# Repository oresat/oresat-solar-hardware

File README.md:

# OreSat Solar Modules

This repo contains the CAD for [OreSat's](oresat.org) solar modules. Part of OreSat's design is a module bus system that spans 1 - 3 U, so each array is its own 1U "panel". Oresat0, a 1U CubeSat, thus has 4 solar modules, and OreSat1, a 2U CubeSat, has 8. This approach has pretty severe drawbacks in terms of solar cell coverage area, but it's extremely flexible for having one design across a bunch of different designs. One nifty part of this design is that each 1u panel has its own **true** maximum power point tracker, with a software-defined MPPT algorithm. We're MPPT elitists - we eschew maximum power point "controllers" and think if it's not doing true power point optimization, you're just doing it wrong.

That and coffee. You're all doing coffee wrong, too, but we don't hold that against you, you don't live in Portland, we understand.

We've flown our GaAs solar cell design, and are currently workingon our silicon design.

# Design Notes

**Status, design, construction, and testing information can be found in the [OreSat Solar Module Design Notes](https://docs.google.com/document/d/1mogZjYhJievwLsnVkg4Q0sEF9xPMA5q7KPciky3YWKE/edit?usp=sharing).**

# Pretty Pictures

## LICENSE

Copyright the Portland State Aerospace Society, 2025.

This source describes Open Hardware that is licensed under CERN-OHL-S v2, or any later version.

You may redistribute and modify this source and make products using it under the terms of the CERN-OHL-S v2 (https://ohwr.org/cern_ohl_s_v2.txt).

This source is distributed WITHOUT ANY EXPRESS OR IMPLIED WARRANTY, INCLUDING OF MERCHANTABILITY, SATISFACTORY QUALITY AND FITNESS FOR A PARTICULAR PURPOSE. Please see the CERN-OHL-S v2 for applicable conditions.

Source location: https://github.com/oresat/

If you require a different license for this open hardware project, please contact us at [oresat@pdx.edu](mailto:oresat@pdx.edu).

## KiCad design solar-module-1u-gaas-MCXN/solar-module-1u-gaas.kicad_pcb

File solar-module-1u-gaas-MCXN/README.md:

---
title: "**OreSat Solar Module with GaAs Cells and MCXN processor**"
subtitle: |
  **Fabrication and Assembly Information**\
  For build TIME-STAMP
fontsize: 10pt
geometry:
  - margin=0.5in
toc: true
toc-depth: 2
colorlinks: true
urlcolor: blue
---

\newpage

# About this Board

## Board Description

This PCB is for the OreSat "1U" solar module which is used for all OreSat 1 - 3U designs. It has GaAs and Si solar cell variants, as well as STM32 and MCXN microcontorller variants. This design is the GaAs + MCXN version. It is scheduled to fly on OreSat1. 

The solar module takes power from the solar cells and does true maximum power point tracking (MPPT) using the Perturb and Observe ("P&O") method. It boosts the cell voltage up to 8.2 V in order to directly charge the batteries.

## Documentation Links

- Git repository: <https://github.com/oresat/oresat-solar-hardware>
- [Design Notes](https://docs.google.com/document/d/1mogZjYhJievwLsnVkg4Q0sEF9xPMA5q7KPciky3YWKE/edit?usp=sharing)

## Documentation Files

| Filename                        | Notes                                    |
| ------------------------------- | ---------------------------------------- |
| README.pdf                      | This README file                         |
| PROJECT-NAME-outline.dxf        | Board outline (with holes) in DXF format |
| PROJECT-NAME-pcba.step          | 3D model of PCBA (with components)       |
| PROJECT-NAME-render-bot.jpg     | Render of the top of the 3D model        |
| PROJECT-NAME-render-bot.jpg     | Render of the bottom of the 3D model     |
| PROJECT-NAME-schematic.pdf      | PDF of board schematics                  |

## Contact Information

- Website: <https://www.oresat.org/>
- Email: <oresat@pdx.edu>
- Instagram: @pdxaerospace

## Board Renders

{width=50%}
{width=50%}

\newpage

# Printed Circuit Board (PCB) Fabrication Information

## Board Info

- 4 layer board
- Bounding box is 83.0 x 100.0 mm
- Board thickness is 1.59 mm

## Board Requirements

- Design Rules
    - Minimum Trace / Space design rules
       - Outer layers: 0.127 mm (5.0 mil) / 0.127 mm (5.0 mil)
       - Inner layers: 0.127 mm (5.0 mil) / 0.127 mm (5.0 mil)
    - Outer dimension router tolerance: +/- 0.254 mm (10.0 mil)
    - Hole placement tolerance: +/- 0.075 mm (3.0 mil)
    - Inner tab routed slot tolerance: +/- 0.254 mm (10.0 mil)
- Drills
   - Drill Positional Tolerance: 0.051 mm (2.0 mil)
   - Drill Size tolerance: +/- 0.064 mm (2.5 mil)
- Plated/Un-plated holes
  - Via/PTH minimum diameter: 0.254 mm (10 mil)
  - Via/PTH minimum annulus: 0.102 mm (4 mil) radius
- Outline/Routing
  - This board requires a 1 mm router bit.
- Slots/Cutouts
  - There are six cutouts in the board.
- There are 3 fiducials on the top layer.
- Panel tabs ("mouse bites")
   - Card edges must be smooth; no mouse bites or other intrusions into the card outline.
   - If external mouse bites are required, minimize and customer will remove by hand before assembly.
- If not otherwise specified, build to IPC 6012 Class 2 or better.

## Stackup /  Materials

- Outside copper layers is 1 oz Cu after plating (0.043 mm / 1.7 mil)
- Inside copper layers are 0.5 oz Cu (0.018 mm / 0.7 mil)
- There are no requirements on the prepreg or core of this four layer stackup.
- Board Surface treatment should be ENIG, althogh immersion Silver is acceptable.
- White silkscreen on top and bottom surface
- Taiyo PSR-4000 or equivalent soldermask on top and bottom, no requirements for color.

## Array / Panel Information

- Coordinate with Contract Manufacturer (CM) for optimal size of this panel.
- If no feedback from CM, then produce single boards (no panel).

## Fabrication Files

### IPC-2581 File

| Filename                 | Notes                                   |
| ------------------------ | --------------------------------------- |
| PROJECT-NAME-ipc2581.xml | IPC-2581 board information file         |

### Legacy PCB Files

| Filename                      | Notes                                         |
| ------------------------------| --------------------------------------------- |
| PROJECT-NAME-Edge_Cuts.gbr    | RS274X file for the dimension (outline) layer |
| PROJECT-NAME-F_Silkscreen.gbr | RS274X file for the top silkscreen            |
| PROJECT-NAME-F_Mask.gbr       | RS274X file for the top soldermask            |
| PROJECT-NAME-F_Cu.gbr         | RS274X file for the top copper layer          |
| PROJECT-NAME-In1_Cu.gbr       | RS274X file for the layer 2 copper            |
| PROJECT-NAME-In2_Cu.gbr       | RS274X file for the layer 3 copper            |
| PROJECT-NAME-B_Cu.gbr         | RS274X file for the bottom copper layer       |
| PROJECT-NAME-B_Mask.gbr       | RS274X file for the bottom soldermask         |
| PROJECT-NAME-B_Silkscreen.gbr | RS274X file for the bottom silkscreen         |
| PROJECT-NAME-NPTH.drl         | Excellon file for non-plated through holes    |
| PROJECT-NAME-PTH.drl          | Excellon file for plated through holes        | 

\newpage

# Printed Circuit Board Assembly (PCBA) Information

## Assembly Info

- All components are on the top side of the board.
- This PCBA uses only surface mount (SMT) components.

## Assembly Requirements

- Assemble to IPC Class 2 or better
- Bake components that are not moisture sealed to appropriate levels as required.
- Solder paste MUST be leaded.
- Aqueous flux and wash strongly preferred.
   - Clean to NASA Standard "Visibly Clean (VC)": No particles or residues are visible to the naked eye.
- No conformal coating.
- Ship in antistatic protective bag

## Component Specific Assembly Information

- U2 and U7 are hand installed upside down; see ["PSAS SOP - TMP101 Mounting on Solar MOdules"](https://docs.google.com/document/d/1C_-naV0ThPKOAYU6vSqqT_bxouM6lSOQ0vK8YNHYac8/edit?usp=sharing).
- Solar Cells D2 and D6 are hand placed; see ["PSAS SOP - Solar Cell mounting with PSA"](https://docs.google.com/document/d/1PRLbhDLpztdpU8TQuk0uR0zjref0UoxRCXlIfN_OXDI/edit?usp=sharing).

## Assembly Files

### IPC-2581 File

| Filename                 | Notes                           |
| ------------------------ | ------------------------------- |
| PROJECT-NAME-ipc2581.xml | IPC-2581 board information file |

### Bill of Materials (BOM)

| Filename             | Description                            |
| -------------------- | -------------------------------------- |
| PROJECT-NAME-bom.csv | BOM in Comma Separated Variable format |

### Solder Paste Stencils

| Filename                 | Notes                                            |
| ------------------------ | ------------------------------------------------ |
| PROJECT-NAME-B_Paste.gbr | RS274X file for top/front solder paste stencil   |
| PROJECT-NAME-F_Paste.gbr | RS274X file for bottom/back solder paste stencil |

### Mounting/Placement Location

| Filename            | Description                                 |
| ------------------- | ------------------------------------------- |
| PROJECT-NAME.pos | Pick and place locations for components     |

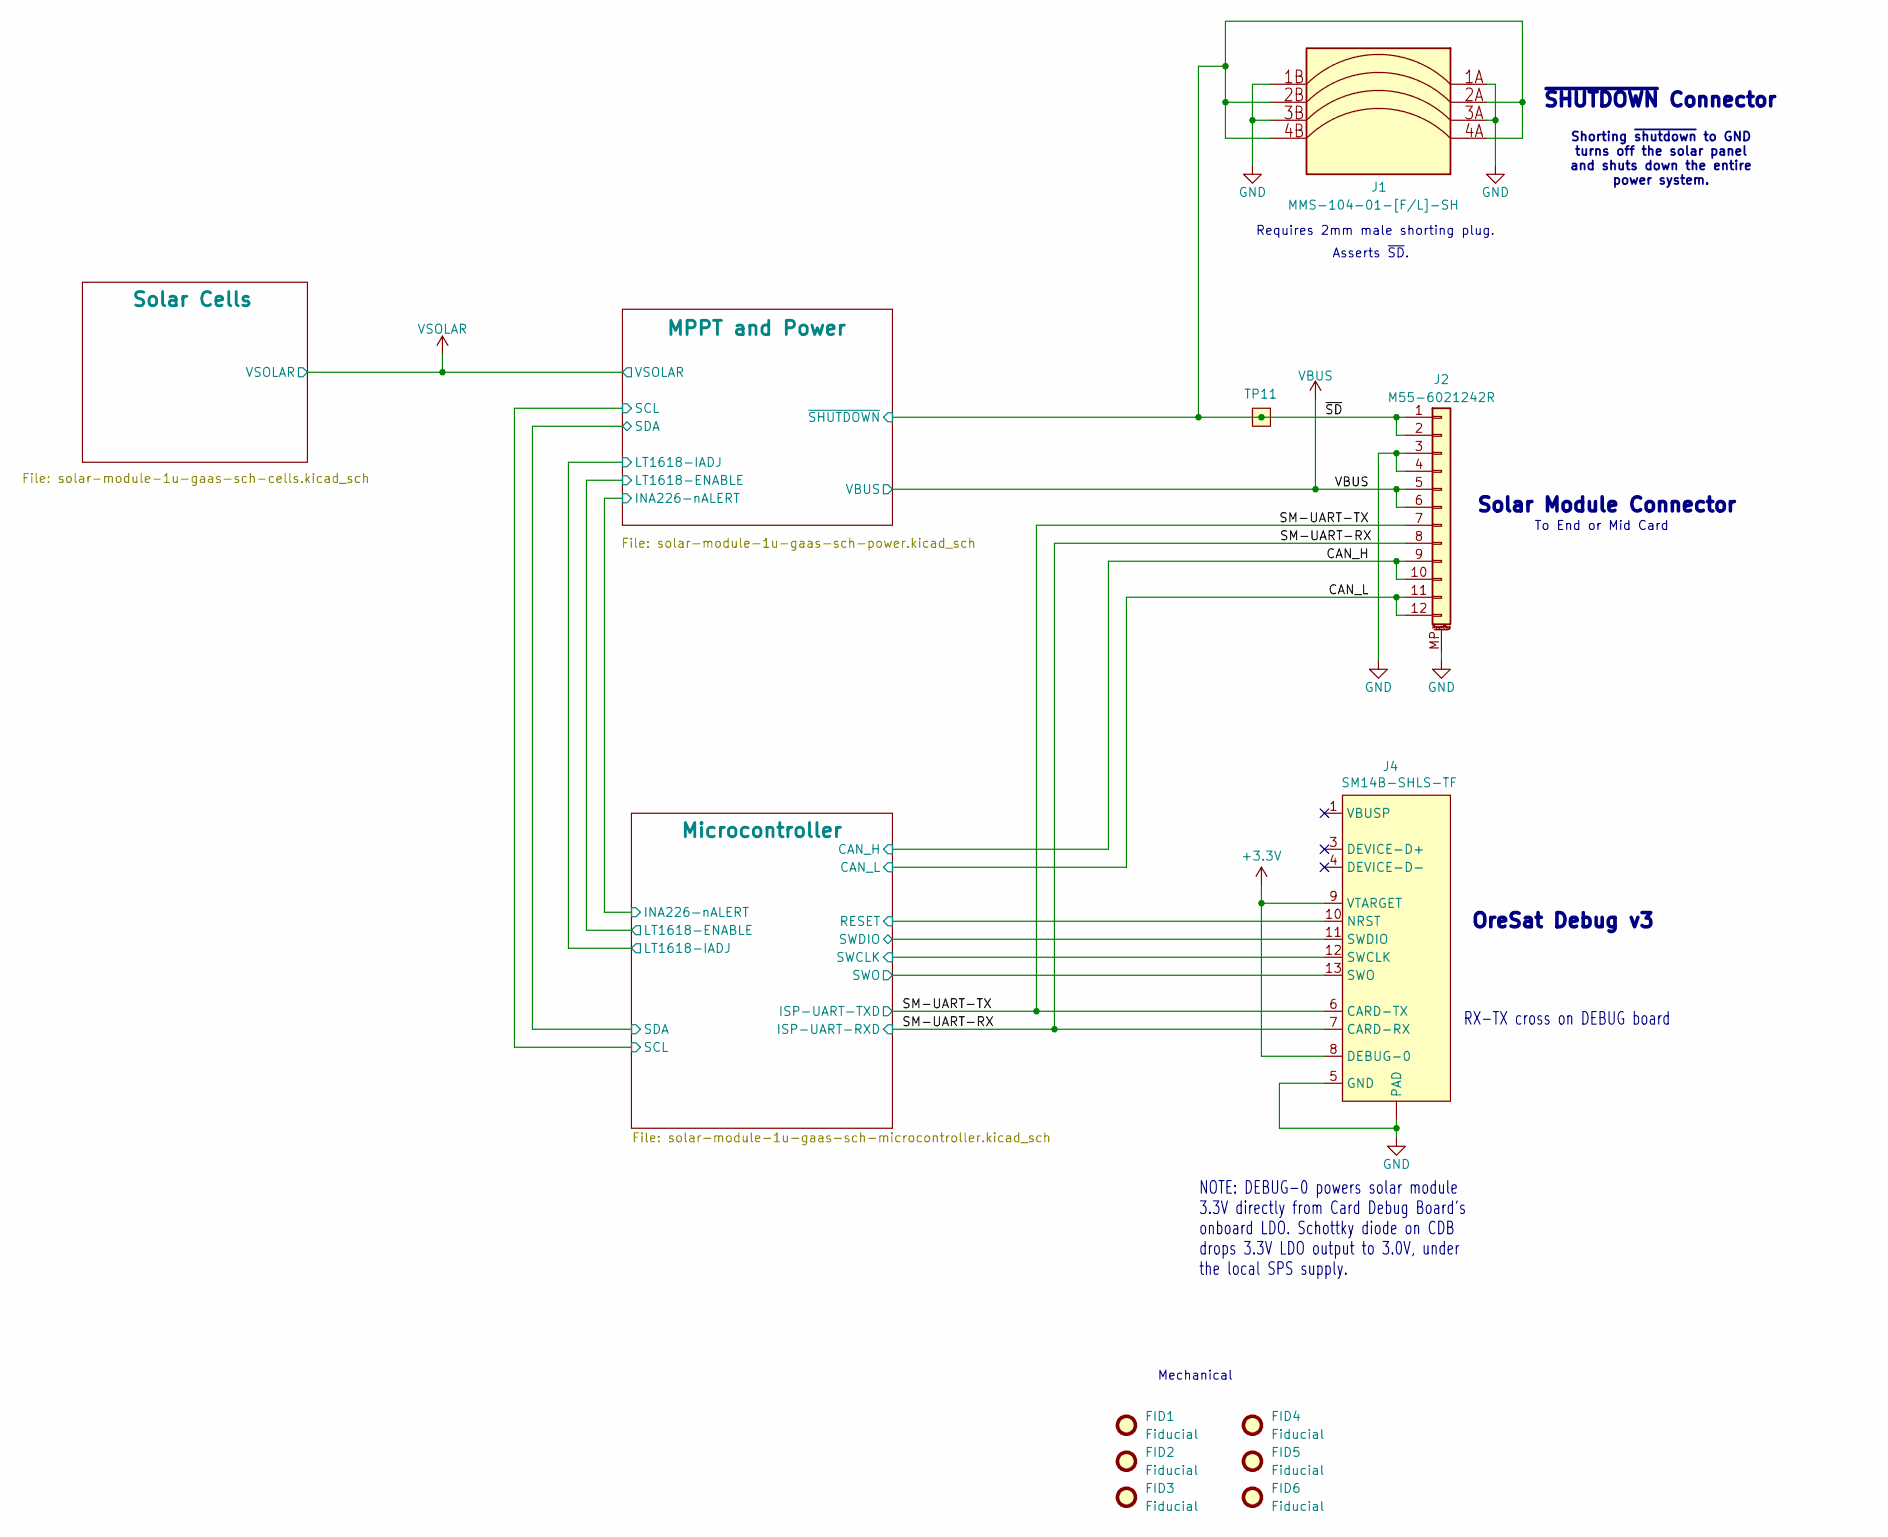
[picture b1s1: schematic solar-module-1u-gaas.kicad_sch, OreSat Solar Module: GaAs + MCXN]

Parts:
FID1, FID2, FID3, FID4, FID5, FID6: Fiducial; Fiducial_1mm_Mask2mm
J1: MMS-104-01-[F/L]-SH; SAMTEC-MMS-104-02-X-SH; MPN MMS-104-02-L-SH
J2: M55-6021242R; J-Harwin-M55-60X1242R; MPN M55-6021242R
J4: SM14B-SHLS-TF; J-JST-SM14BSHLSTF; MPN SM14B-SHLS-TF
TP11: TEST-POINT-LARGE-SQUARE; TestPoint-0.75mm-th

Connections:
+3.3V: J4.8 (DEBUG-0), J4.9 (VTARGET); also elsewhere on the board
/CAN_H: J2.9, J2.10; also elsewhere on the board
/CAN_L: J2.11, J2.12; also elsewhere on the board
/Microcontroller/RESET: J4.10 (NRST); also elsewhere on the board
/Microcontroller/SWCLK: J4.12 (SWCLK); also elsewhere on the board
/Microcontroller/SWDIO: J4.11 (SWDIO); also elsewhere on the board
/Microcontroller/SWO: J4.13 (SWO); also elsewhere on the board
/SM-UART-RX: J2.8, J4.7 (CARD-RX); also elsewhere on the board
/SM-UART-TX: J2.7, J4.6 (CARD-TX); also elsewhere on the board
/~SD: J1.2A, J1.2B, J1.4A, J1.4B, J2.1, J2.2, TP11.1 (1_1); also elsewhere on the board
GND: J1.1A, J1.1B, J1.3A, J1.3B, J2.3, J2.4, J2.MP (MountPin), J4.5 (GND), J4.14 (GND), J4.15 (PAD), J4.16 (PAD); also elsewhere on the board
VBUS: J2.5, J2.6; also elsewhere on the board

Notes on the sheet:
RX-TX cross on DEBUG board
Mechanical
Asserts ~{SD}.
Requires 2mm male shorting plug.
OreSat Debug v3
Solar Module Connector
Shorting ~{shutdown} to GND turns off the solar panel and shuts down the entire power system.
To End or Mid Card
NOTE: DEBUG-0 powers solar module 3.3V directly from Card Debug Board's onboard LDO. Schottky diode on CDB drops 3.3V LDO output to 3.0V, under the local SPS supply.
~{SHUTDOWN} Connector

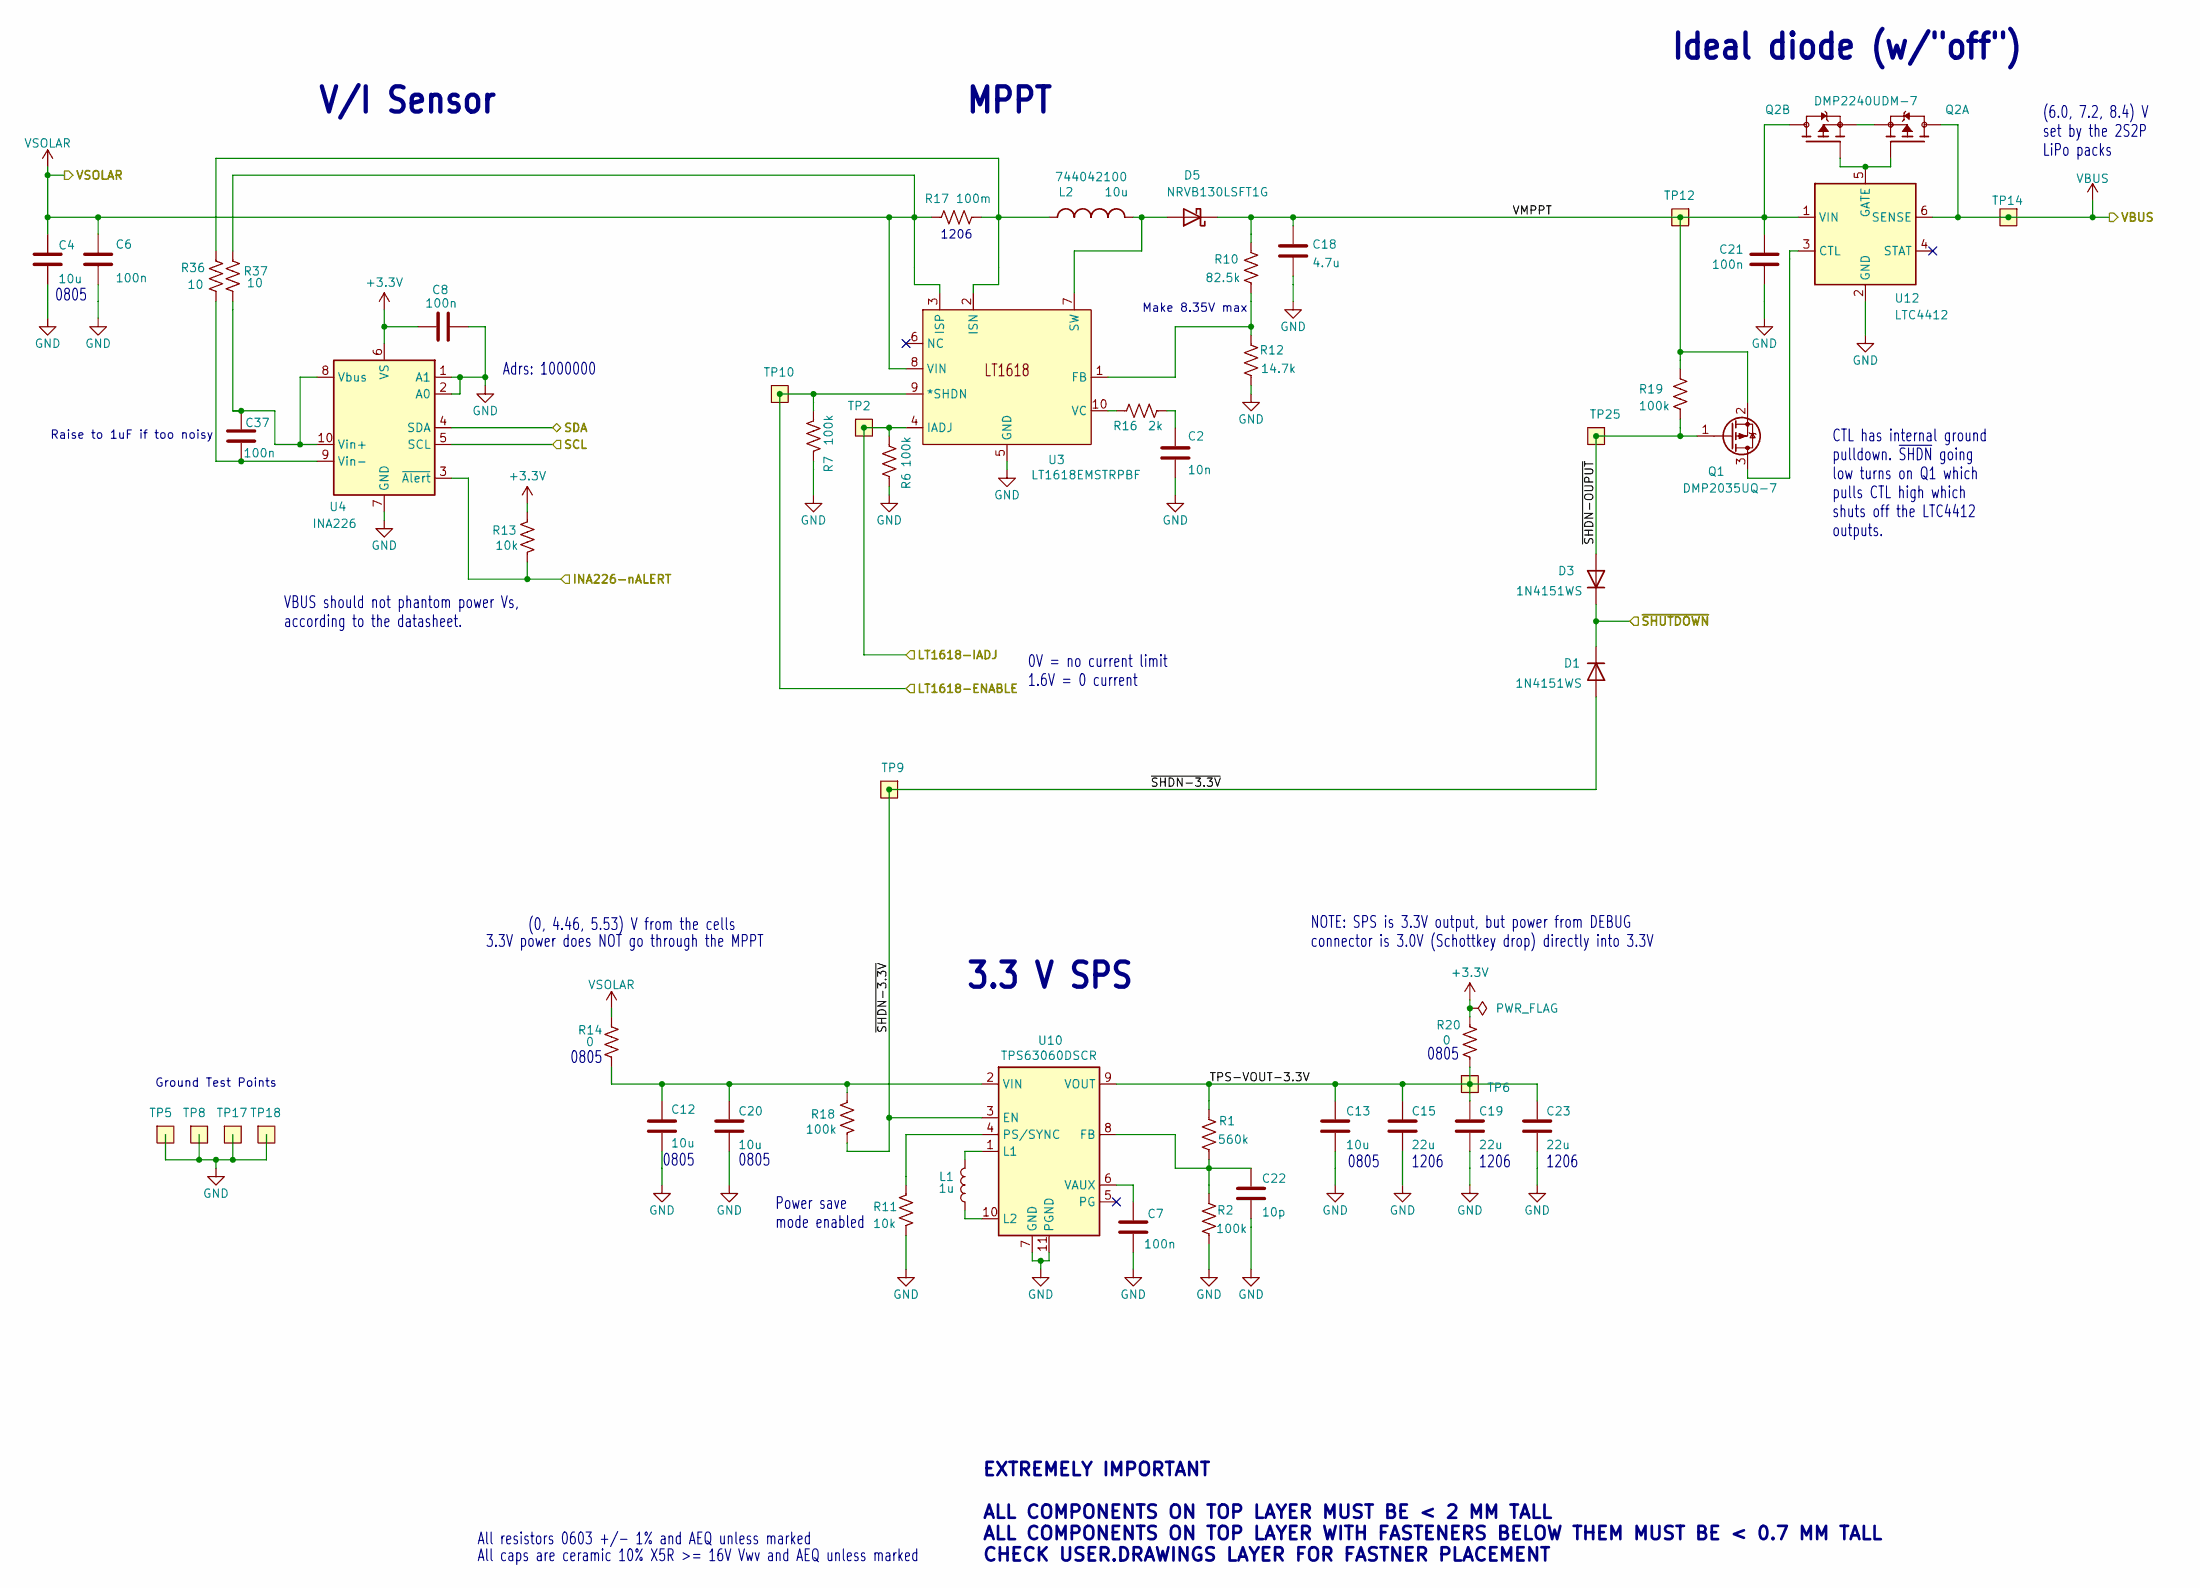
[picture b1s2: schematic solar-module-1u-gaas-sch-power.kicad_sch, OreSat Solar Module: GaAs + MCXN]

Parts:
C2: 10n; 0603-C-NOSILK; MPN C0603C103J5RACAUTO
C4, C12, C13, C20: 10u; 0805-C-NOSILK; MPN GRT21BC71E106KE13K
C6, C7, C8, C21, C37: 100n; 0603-C-NOSILK; MPN C0603C104K5RACAUTO
C15, C19, C23: 22u; 1206-C; MPN GRT31CC81C226KE01L
C18: 4.7u; 0603-C-NOSILK; MPN GRT188C71C475KE13D
C22: 10p; 0603-C-NOSILK; MPN C0603C100J1GACAUTO
D1, D3: 1N4151WS; D_SOD-323F; MPN 1N4151WS-E3-08
D5: NRVB130LSFT1G; D_SOD-123; MPN NRVB130LSFT1G
L1: 1u; IND_1226AS-H-1R0N=P2; MPN 1227AS-H-1R0N=P2
L2: 10u; 744042100; MPN 744042100
Q1: DMP2035UQ-7; SOT-23; MPN DMP2035UQ-7
Q2: DMP2240UDM-7; SOT-23-6; MPN DMP2240UDM-7
R1: 560k; 0603-C-NOSILK; MPN RMCF0603FT560K
R2, R6, R7, R18, R19: 100k; 0603-C-NOSILK; MPN RMCF0603FT100K
R10: 82.5k; 0603-C-NOSILK; MPN RMCF0603FT82K5
R11, R13: 10k; 0603-C-NOSILK; MPN RMCF0603FT10K0
R12: 14.7k; 0603-C-NOSILK; MPN RMCF0603FT14K7
R14, R20: 0; 0805-C-NOSILK; MPN RMCF0805ZG0R00
R16: 2k; 0603-C-NOSILK; MPN RMCF0603FT2K00
R17: 100m; 1206-C; MPN CSR1206FTR100
R36, R37: 10; 0603-C-NOSILK; MPN RMCF0603FT10R0
TP2, TP5, TP6, TP8, TP9, TP10, TP12, TP14, TP17, TP18, TP25: TEST-POINT-LARGE-SQUARE; TestPoint-0.75mm-th
U3: LT1618EMSTRPBF; MSOP-10_MS; MPN IC REG BOOST ADJ 1.5A 10MSOP
U4: INA226; TSSOP-10_3x3mm_P0.5mm; MPN INA226AIDGST
U10: TPS63060DSCR; Texas_S-PWSON-N10; MPN IC REG BUCK BOOST ADJ 2A 10WSON
U12: LTC4412; TSOT-23-6; MPN LTC4412ES6#TRPBF

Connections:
+3.3V: C8.1, R13.2, R20.1, U4.6 (VS); also elsewhere on the board
/MPPT and Power/INA226-nALERT: R13.1, U4.3 (~Alert); also elsewhere on the board
/MPPT and Power/LT1618-ENABLE: R7.1, TP10.1 (1_1), U3.9 (*SHDN); also elsewhere on the board
/MPPT and Power/LT1618-IADJ: R6.1, TP2.1 (1_1), U3.4 (IADJ); also elsewhere on the board
/MPPT and Power/TPS-VOUT-3.3V: C13.1, C15.1, C19.1, C23.1, R1.2, R20.2, TP6.1 (1_1), U10.9 (VOUT)
/MPPT and Power/VMPPT: C18.1, C21.1, D5.1 (K), Q1.2 (S), Q2.4 (D), R10.2, R19.2, TP12.1 (1_1), U12.1 (VIN)
/MPPT and Power/~SHDN-3.3V: D1.2 (A), R18.1, TP9.1 (1_1), U10.3 (EN)
/MPPT and Power/~SHDN-OUPUT: D3.2 (A), Q1.1 (G), R19.1, TP25.1 (1_1)
/Microcontroller/SCL: U4.5 (SCL); also elsewhere on the board
/Microcontroller/SDA: U4.4 (SDA); also elsewhere on the board
/~SD: D1.1 (K), D3.1 (K); also elsewhere on the board
GND: C2.2, C4.2, C6.2, C7.2, C8.2, C12.2, C13.2, C15.2, C18.2, C19.2, C20.2, C21.2, C22.2, C23.2, R2.1, R6.2, R7.2, R11.1, R12.1, TP5.1 (1_1), TP8.1 (1_1), TP17.1 (1_1), TP18.1 (1_1), U3.5 (GND), U4.1 (A1), U4.2 (A0), U4.7 (GND), U10.7 (GND), U10.11 (PGND), U12.2 (GND); also elsewhere on the board
unnamed: C2.1, R16.1
unnamed: D5.2 (A), L2.2, U3.7 (SW)
unnamed: Q1.3 (D), U12.3 (CTL)
unnamed: Q2.1 (G), Q2.3 (G), U12.5 (GATE)
unnamed: Q2.2 (S), Q2.5 (S)
unnamed: R10.1, R12.2, U3.1 (FB)
unnamed: L2.1, R17.2, R36.1, U3.2 (ISN)
unnamed: R16.2, U3.10 (VC)
unnamed: C37.1, R37.1, U4.8 (Vbus), U4.10 (Vin+)
unnamed: C37.2, R36.2, U4.9 (Vin-)
unnamed: C22.1, R1.1, R2.2, U10.8 (FB)
unnamed: L1.2, U10.1 (L1)
unnamed: L1.1, U10.10 (L2)
unnamed: R11.2, U10.4 (PS/SYNC)
unnamed: C7.1, U10.6 (VAUX)
unnamed: C12.1, C20.1, R14.1, R18.2, U10.2 (VIN)
VBUS: Q2.6 (D), TP14.1 (1_1), U12.6 (SENSE); also elsewhere on the board
VSOLAR: C4.1, C6.1, R14.2, R17.1, R37.2, U3.3 (ISP), U3.8 (VIN); also elsewhere on the board

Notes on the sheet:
1206
CTL has internal ground pulldown. ~{SHDN} going low turns on Q1 which pulls CTL high which shuts off the LTC4412 outputs.
(0, 4.46, 5.53) V from the cells
0805
Ground Test Points
Make 8.35V max
Raise to 1uF if too noisy
All resistors 0603 +/- 1% and AEQ unless marked
NOTE: SPS is 3.3V output, but power from DEBUG connector is 3.0V (Schottkey drop) directly into 3.3V
Power save mode enabled
3.3 V SPS
EXTREMELY IMPORTANT ALL COMPONENTS ON TOP LAYER MUST BE < 2 MM TALL ALL COMPONENTS ON TOP LAYER WITH FASTENERS BELOW THEM MUST BE < 0.7 MM TALL CHECK USER.DRAWINGS LAYER FOR FASTNER PLACEMENT
MPPT
All caps are ceramic 10% X5R >= 16V Vwv and AEQ unless marked
Ideal diode (w/"off")
VBUS should not phantom power Vs, according to the datasheet.
3.3V power does NOT go through the MPPT
V/I Sensor
0V = no current limit 1.6V = 0 current
Adrs: 1000000
(6.0, 7.2, 8.4) V set by the 2S2P LiPo packs

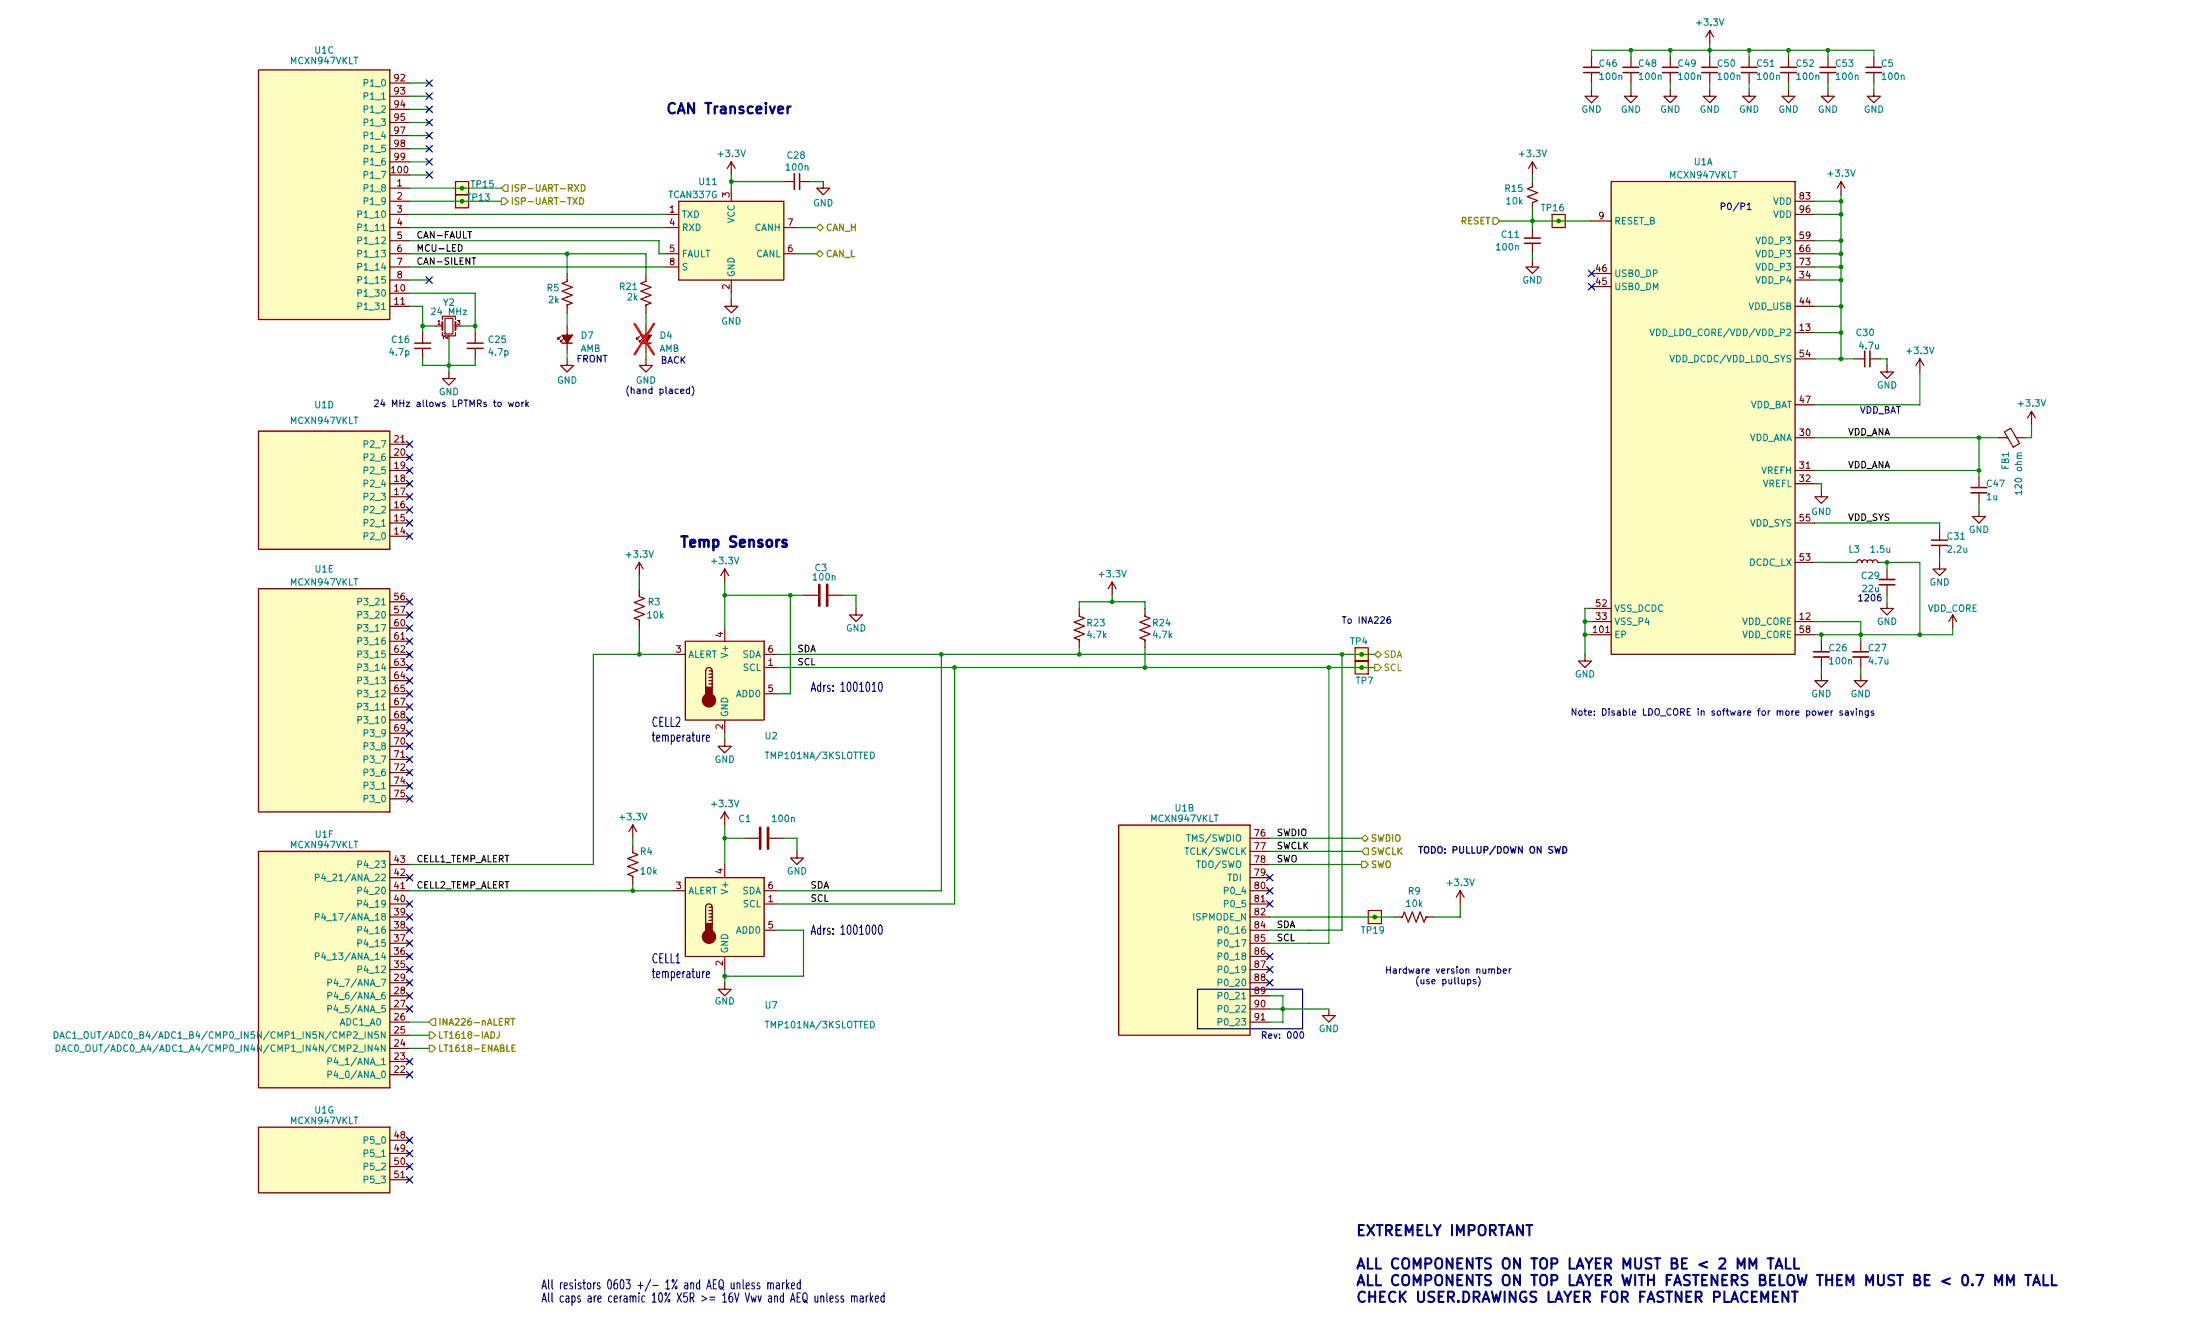
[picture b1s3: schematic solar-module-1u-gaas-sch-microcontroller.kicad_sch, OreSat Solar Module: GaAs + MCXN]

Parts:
C1, C3, C5, C11, C26, C28, C46, C48, C49, C50, C51, C52, C53: 100n; 0603-C-NOSILK; MPN C0603C104K5RACAUTO
C16, C25: 4.7p; 0603-C-NOSILK; MPN C0603C479D5GACAUTO
C27, C30: 4.7u; 0603-C-NOSILK; MPN GRT188C71C475KE13D
C29: 22u; 1206-C; MPN GRT31CC81C226KE01L
C31: 2.2u; 0603-C-NOSILK; MPN GRT188C71E225KE13D
C47: 1u; 0603-C-NOSILK; MPN GRT188R71E105KE13D
D4: AMB; LED_0603_1608Metric; MPN 150060AS75000; not fitted
D7: AMB; LED_0603_1608Metric; MPN 150060AS75000
FB1: 120 ohm; 0805-B-NOSILK; MPN 2508051217Y6
L3: 1.5u; L_0805_2012Metric; MPN SRP2012TMA-1R5M
R3, R4, R9, R15: 10k; 0603-C-NOSILK; MPN RMCF0603FT10K0
R5, R21: 2k; 0603-C-NOSILK; MPN RMCF0603FT2K00
R23, R24: 4.7k; 0603-C-NOSILK; MPN RMCF0603FT4K70
TP4, TP7, TP13, TP15, TP16, TP19: Test-Point; TestPoint-0.75mm-th
U1: MCXN947VKLT; MCXN947KVLT-QFP50P1600X1600X160-101N; MPN MCXN947VKLT
U2, U7: TMP101NA/3KSLOTTED; DBV6-SLOT; MPN TMP101NA/3K
U11: TCAN337G; SOT-23-8; MPN TCAN337GD
Y2: 24 MHz; Crystal_SMD_2016-4Pin_2.0x1.6mm; MPN 830108212309

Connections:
+3.3V: C1.1, C3.1, C5.1, C28.1, C30.1, C46.1, C48.1, C49.1, C50.1, C51.1, C52.1, C53.1, FB1.1, R3.2, R4.2, R9.2, R15.2, R23.2, R24.2, U1.13 (VDD_LDO_CORE/VDD/VDD_P2), U1.34 (VDD_P4), U1.44 (VDD_USB), U1.47 (VDD_BAT), U1.54 (VDD_DCDC/VDD_LDO_SYS), U1.59 (VDD_P3), U1.66 (VDD_P3), U1.73 (VDD_P3), U1.83 (VDD), U1.96 (VDD), U2.4 (V+), U2.5 (ADD0), U7.4 (V+), U11.3 (VCC); also elsewhere on the board
/CAN_H: U11.7 (CANH); also elsewhere on the board
/CAN_L: U11.6 (CANL); also elsewhere on the board
/MPPT and Power/INA226-nALERT: U1.26 (ADC1_A0); also elsewhere on the board
/MPPT and Power/LT1618-ENABLE: U1.24 (DAC0_OUT/ADC0_A4/ADC1_A4/CMP0_IN4N/CMP1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); also elsewhere on the board
/MPPT and Power/LT1618-IADJ: U1.25 (DAC1_OUT/ADC0_B4/ADC1_B4/CMP0_IN5N/CMP1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); also elsewhere on the board
/Microcontroller/CAN-FAULT: U1.5 (P1_12), U11.5 (FAULT)
/Microcontroller/CAN-SILENT: U1.7 (P1_14), U11.8 (S)
/Microcontroller/CELL1_TEMP_ALERT: R3.1, U1.43 (P4_23), U2.3 (ALERT)
/Microcontroller/CELL2_TEMP_ALERT: R4.1, U1.41 (P4_20), U7.3 (ALERT)
/Microcontroller/MCU-LED: R5.1, R21.1, U1.6 (P1_13)
/Microcontroller/RESET: C11.1, R15.1, TP16.1 (1_1), U1.9 (RESET_B); also elsewhere on the board
/Microcontroller/SCL: R24.1, TP7.1 (1_1), U1.85 (P0_17), U2.1 (SCL), U7.1 (SCL); also elsewhere on the board
/Microcontroller/SDA: R23.1, TP4.1 (1_1), U1.84 (P0_16), U2.6 (SDA), U7.6 (SDA); also elsewhere on the board
/Microcontroller/SWCLK: U1.77 (TCLK/SWCLK); also elsewhere on the board
/Microcontroller/SWDIO: U1.76 (TMS/SWDIO); also elsewhere on the board
/Microcontroller/SWO: U1.78 (TDO/SWO); also elsewhere on the board
/Microcontroller/VDD_ANA: C47.1, FB1.2, U1.30 (VDD_ANA), U1.31 (VREFH)
/Microcontroller/VDD_SYS: C31.1, U1.55 (VDD_SYS)
/SM-UART-RX: TP15.1 (1_1), U1.1 (P1_8); also elsewhere on the board
/SM-UART-TX: TP13.1 (1_1), U1.2 (P1_9); also elsewhere on the board
GND: C1.2, C3.2, C5.2, C11.2, C16.2, C25.2, C26.2, C27.2, C28.2, C29.2, C30.2, C31.2, C46.2, C47.2, C48.2, C49.2, C50.2, C51.2, C52.2, C53.2, D4.1 (K), D7.1 (K), U1.32 (VREFL), U1.33 (VSS_P4), U1.52 (VSS_DCDC), U1.89 (P0_21), U1.90 (P0_22), U1.91 (P0_23), U1.101 (EP), U2.2 (GND), U7.2 (GND), U7.5 (ADD0), U11.2 (GND), Y2.2 (G), Y2.4 (G); also elsewhere on the board
unnamed: D4.2 (A), R21.2
unnamed: D7.2 (A), R5.2
unnamed: L3.2, U1.53 (DCDC_LX)
unnamed: R9.1, TP19.1 (1_1), U1.82 (ISPMODE_N)
unnamed: C25.1, U1.10 (P1_30), Y2.3
unnamed: C16.1, U1.11 (P1_31), Y2.1
unnamed: U1.4 (P1_11), U11.4 (RXD)
unnamed: U1.3 (P1_10), U11.1 (TXD)
VDD_CORE: C26.1, C27.1, C29.1, L3.1, U1.12 (VDD_CORE), U1.58 (VDD_CORE)

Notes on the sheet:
To INA226
(hand placed)
Note: Disable LDO_CORE in software for more power savings
P0/P1
Temp Sensors
VDD_BAT
TODO: PULLUP/DOWN ON SWD
1206
CAN Transceiver
Adrs: 1001010
FRONT
Hardware version number (use pullups)
Adrs: 1001000
24 MHz allows LPTMRs to work
CELL2 temperature
EXTREMELY IMPORTANT ALL COMPONENTS ON TOP LAYER MUST BE < 2 MM TALL ALL COMPONENTS ON TOP LAYER WITH FASTENERS BELOW THEM MUST BE < 0.7 MM TALL CHECK USER.DRAWINGS LAYER FOR FASTNER PLACEMENT
Rev: 000
All resistors 0603 +/- 1% and AEQ unless marked
BACK
CELL1 temperature
All caps are ceramic 10% X5R >= 16V Vwv and AEQ unless marked

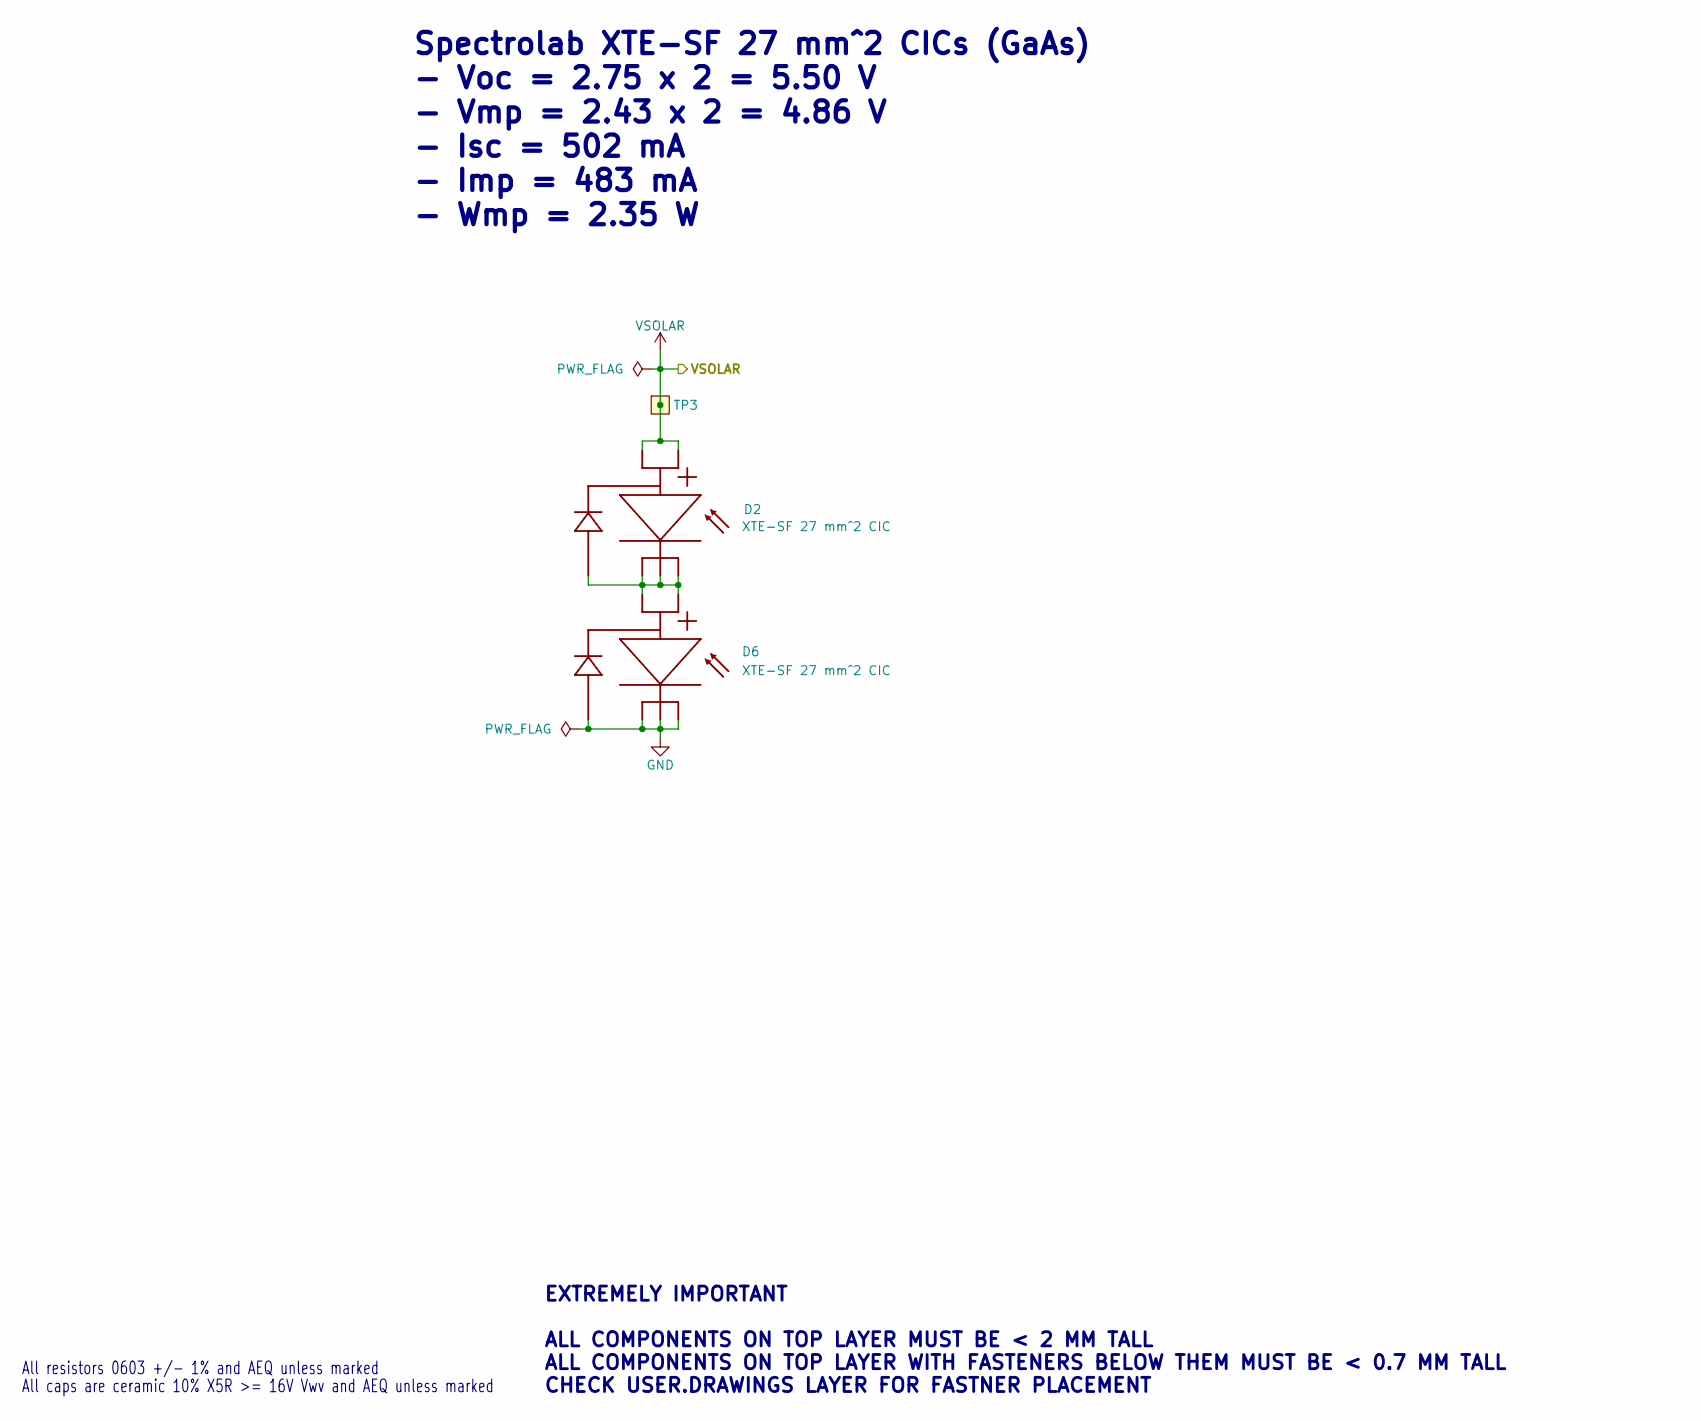
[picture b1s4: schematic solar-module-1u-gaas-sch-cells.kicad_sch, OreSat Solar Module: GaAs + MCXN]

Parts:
D2, D6: XTE-SF 27 mm^2 CIC; SPECTROLAB-XTE-SF-SLOTTED; MPN XTE-SF 27 mm^2 CIC
TP3: TEST-POINT-LARGE-SQUARE; TestPoint-0.75mm-th

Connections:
GND: D6.NEG1 (C1), D6.NEG2 (C2), D6.NEG3 (C3), D6.NEG4 (C4); also elsewhere on the board
unnamed: D2.NEG1 (C1), D2.NEG2 (C2), D2.NEG3 (C3), D2.NEG4 (C4), D6.POS1 (A1), D6.POS2 (A2)
VSOLAR: D2.POS1 (A1), D2.POS2 (A2), TP3.1 (1_1); also elsewhere on the board

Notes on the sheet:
All resistors 0603 +/- 1% and AEQ unless marked
Spectrolab XTE-SF 27 mm^2 CICs (GaAs) - Voc = 2.75 x 2 = 5.50 V - Vmp = 2.43 x 2 = 4.86 V - Isc = 502 mA - Imp = 483 mA - Wmp = 2.35 W
EXTREMELY IMPORTANT ALL COMPONENTS ON TOP LAYER MUST BE < 2 MM TALL ALL COMPONENTS ON TOP LAYER WITH FASTENERS BELOW THEM MUST BE < 0.7 MM TALL CHECK USER.DRAWINGS LAYER FOR FASTNER PLACEMENT
All caps are ceramic 10% X5R >= 16V Vwv and AEQ unless marked
